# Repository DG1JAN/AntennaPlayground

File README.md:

# AntennaPlayground

In this Repro you will find several designs (mostly derived from my UniBaLun Project) to suport antenna building (EFHW and wire Dipols)

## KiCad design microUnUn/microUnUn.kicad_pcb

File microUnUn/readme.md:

# MicroUnUn
a PCB for a very lightweight qrp (maximum 10W SSB & CW or 5W on FT8) 1:49 UnUn

BOM:
- Amdion FT82-43 (FairRite 5943000601)
- 1m Enamel-coated copper wire (0.5mm to 0.7mm will be OK)
- 100pF Capaciator SMD 605 Type
- PCB-Edge Mount SMA Plug (also Socket for direct connection to the radio will work, but use a wire as counterpoise in this case!)
- 2mm "gold" Bana Plug 

You can also test a combination of FairRite 59430000601 and 5943001101 Torroids (see Pictzre below), According my measuremenst this results in a ~10% improved efficency over a FT82-43 or FT114-43). If you like pls have a look to my report:
https://github.com/DG1JAN/UniBalun/blob/main/20230620_EFHW_UnUn_efficiency_meas.pdf

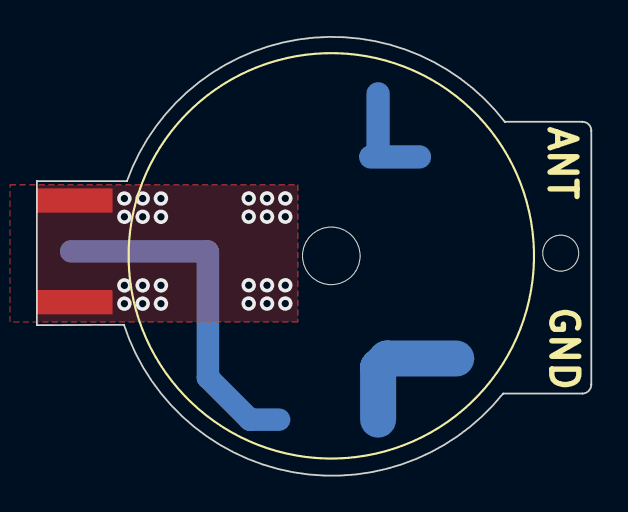
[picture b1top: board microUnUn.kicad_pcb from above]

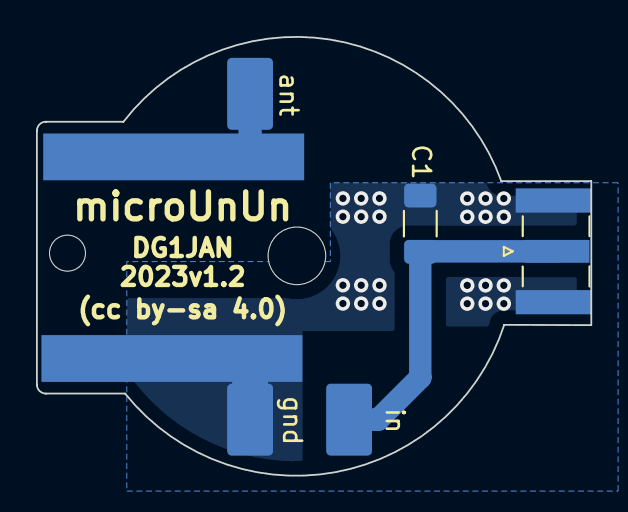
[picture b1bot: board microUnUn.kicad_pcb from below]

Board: 2 copper layers, 30.8 x 24.4 mm, 5 parts (4 on the bottom side), 3 nets.

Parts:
C1: 100pF; C_1206_3216Metric_Pad1.33x1.80mm_HandSolder
H1, H2: MountingHole_Pad; 2mmJack
J1: BNC; SMA_Samtec_SMA-J-P-X-ST-EM1_EdgeMount
U1: Core; FT82_Balun

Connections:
GND: C1.2, H2.1, J1.2 (Ext), U1.1 (gnd)
unnamed: C1.1, J1.1 (In), U1.2 (a)
unnamed: H1.1, U1.3 (x)

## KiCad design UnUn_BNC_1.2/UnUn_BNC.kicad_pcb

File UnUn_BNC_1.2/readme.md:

# UnUn_BNC
a PCB for a lightweight qrp (maximum 10W SSB & CW or 5W on FT8) 1:49  (or 1:9) UnUn
derived from my UniBalun Project (https://github.com/DG1JAN/UniBalun)

This PCB has the smal avantage over the UbiBalun, that you dont need need a jumper and that the "A" Pad on top is fixed connected to GND. So you
can add there a counterpois (esp. if used as 1:9 UnUn). 

BOM:
- Amdion FT82-43 (FairRite 5943000601) or FT114-43 (FairRite 5943001001)
- 1m Enamel-coated copper wire (0.5mm to 0.7mm will be fine, on the Ft114 also 1mm will fit)
- 100pF Capaciator, e.g. TDK CC45SL3FD101JYVNA
- BNC Socket, the Footprint supports multiple options:
    - Molex 73101
    - Amphenol B6252H7 / Telegärtner J01001A0038 (or similar)
    - PCB-Edge Mount SMA (e.g.
- 4mm "gold" Bana Plug (e.g. https://www.amazon.de/gp/product/B07VYSN74H/ref=ppx_yo_dt_b_asin_title_o01_s00?ie=UTF8&th=1)

You can also test a combination of FairRite 59430000601 and 5943001101 Torroids (see Pictzre below), According my measuremenst this results in a ~10% improved efficency over a FT82-43 or FT114-43). If you like pls have a look to my report:
https://github.com/DG1JAN/UniBalun/blob/main/20230620_EFHW_UnUn_efficiency_meas.pdf

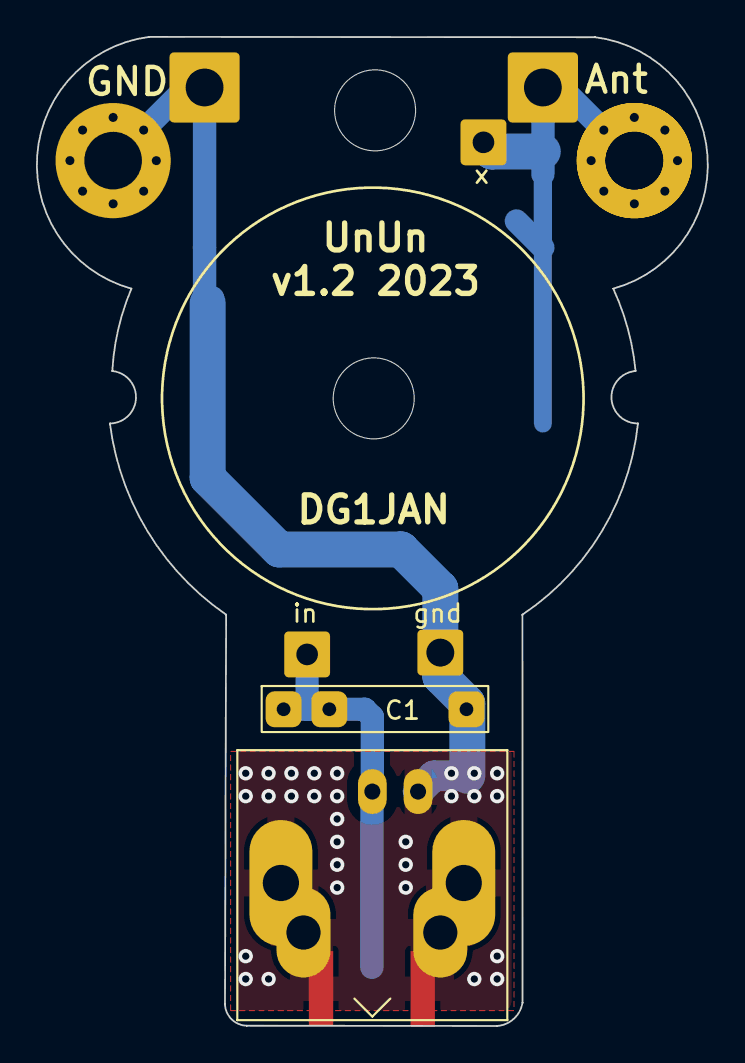
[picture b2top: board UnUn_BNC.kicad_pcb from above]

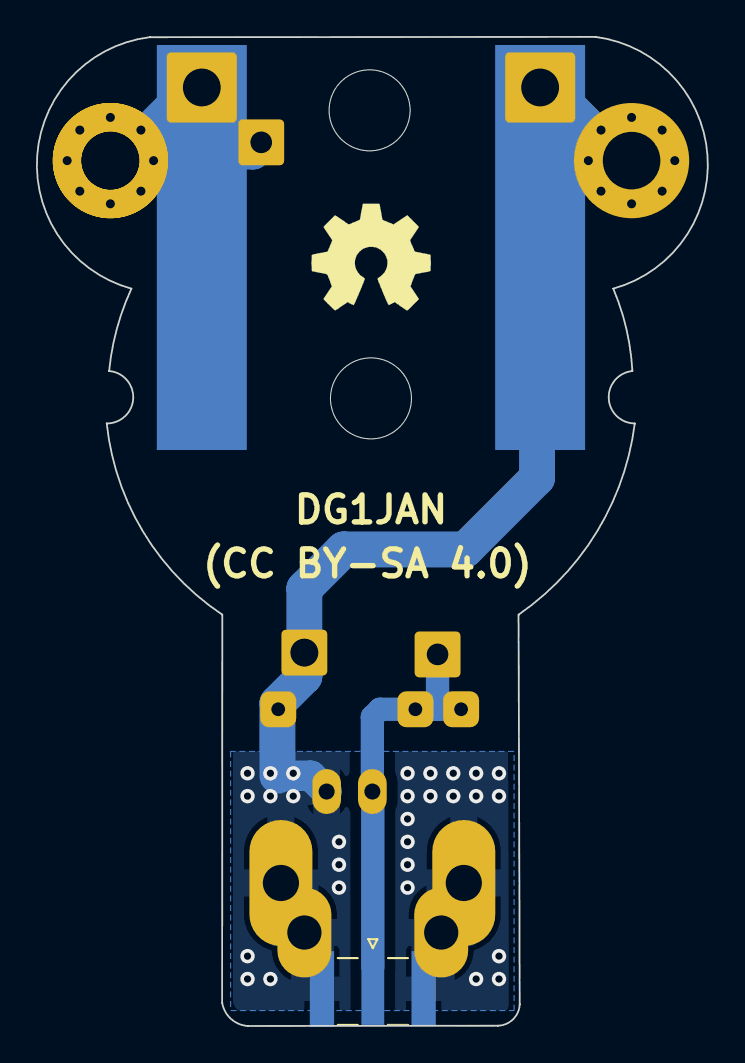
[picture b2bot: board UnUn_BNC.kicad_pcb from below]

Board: 2 copper layers, 37.3 x 55.0 mm, 10 parts (2 on the bottom side), 3 nets.

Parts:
C1: 100pF; THT_cap
H1: B; MountingHole_3.2mm_M3_Pad
H5, H5#2: MountingHole; MountingHole_4.5mm
J1: BNC; BNC_Amphenol_B6252HB-NPP3G-50_Horizontal
J3: B_THT_Pad; SolderWire-1.5sqmm_1x01_D1.7mm_OD3.9mm
J4: B_SMD_PAD; 4mmJack
J5: A_THT_Pad; SolderWire-1.5sqmm_1x01_D1.7mm_OD3.9mm
J6: A_SMD_PAD; 4mmJack
U2: Core; FT82_Balun

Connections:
GND: C1.2, J1.2 (Ext), J5.1, J6.1, U2.1 (a)
unnamed: C1.1, J1.1 (In), U2.4 (b')
unnamed: H1.1, J3.1, J4.1, U2.5 (x)

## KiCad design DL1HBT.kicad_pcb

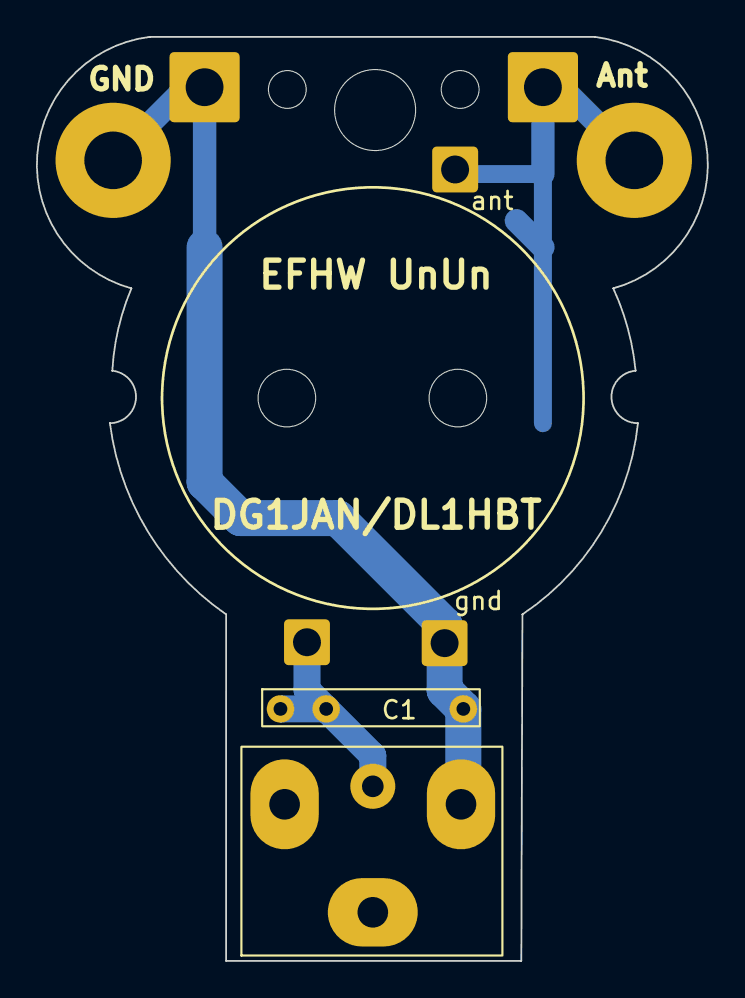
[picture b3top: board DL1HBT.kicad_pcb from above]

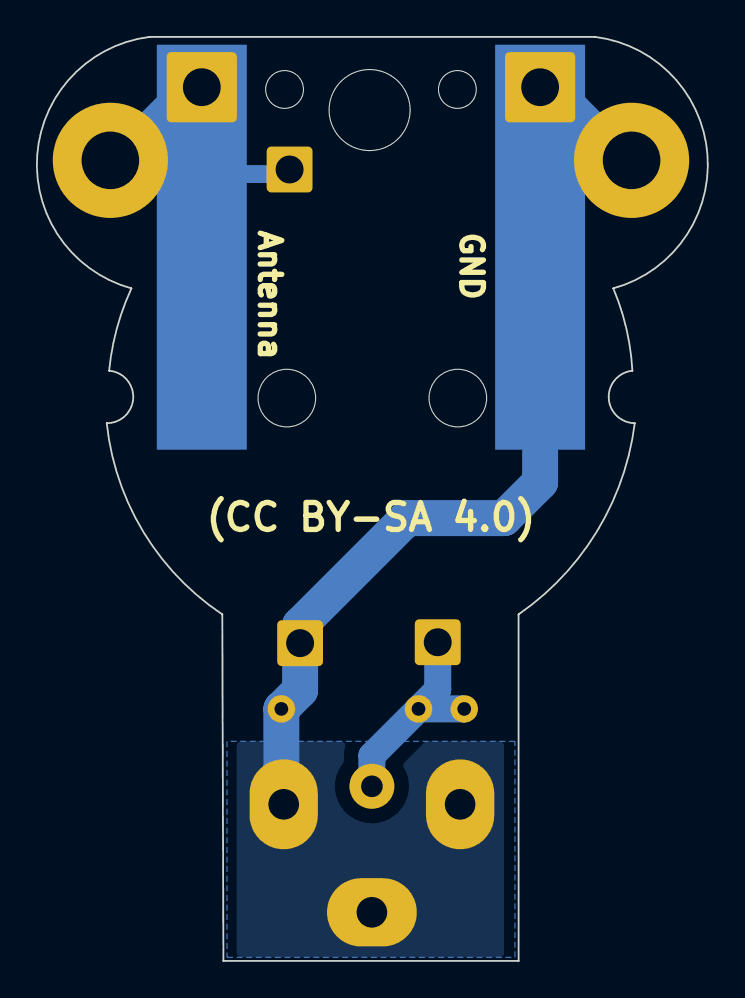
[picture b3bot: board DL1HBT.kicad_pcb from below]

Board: 2 copper layers, 37.3 x 51.3 mm, 12 parts (2 on the bottom side), 3 nets.

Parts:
C1: 100pF; THT_cap
H1: B; MountingHole_3.2mm_M3_Pad
H2: A; MountingHole_3.2mm_M3_Pad
H3, H4: MountingHole; MountingHole_2.1mm
H5: MountingHole; MountingHole_4.5mm
J1: BNC; Elecbee_BNC
J3: B_THT_Pad; SolderWire-1.5sqmm_1x01_D1.7mm_OD3.9mm
J4: B_SMD_PAD; 4mmJack
J5: A_THT_Pad; SolderWire-1.5sqmm_1x01_D1.7mm_OD3.9mm
J6: A_SMD_PAD; 4mmJack
U2: Core; FT82_Balun

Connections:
GND: C1.2, H2.1, J1.2 (Ext), J5.1, J6.1, U2.1 (gnd)
unnamed: C1.1, J1.1 (In), U2.2 (trx)
unnamed: H1.1, J3.1, J4.1, U2.3 (ant)

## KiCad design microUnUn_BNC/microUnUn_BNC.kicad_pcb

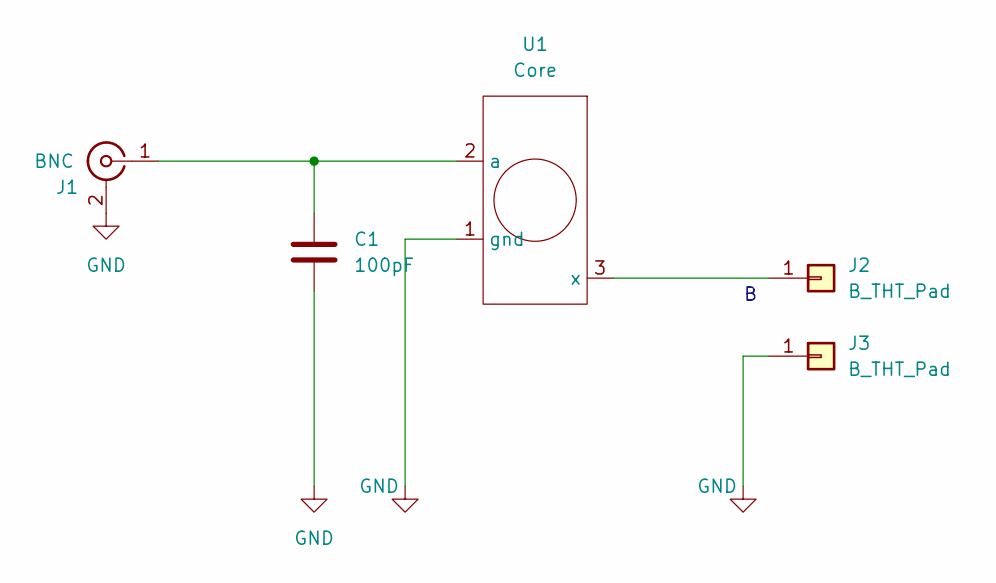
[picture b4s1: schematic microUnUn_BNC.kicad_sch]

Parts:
C1: 100pF; THTSMD_cap
J1: BNC; Elecbee_BNC
J2, J3: B_THT_Pad; SolderWire-1.5sqmm_1x01_D1.7mm_OD3.9mm
U1: Core; FT82_Balun

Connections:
GND: C1.2, J1.2 (Ext), J3.1, U1.1 (gnd)
unnamed: C1.1, J1.1 (In), U1.2 (a)
unnamed: J2.1, U1.3 (x)

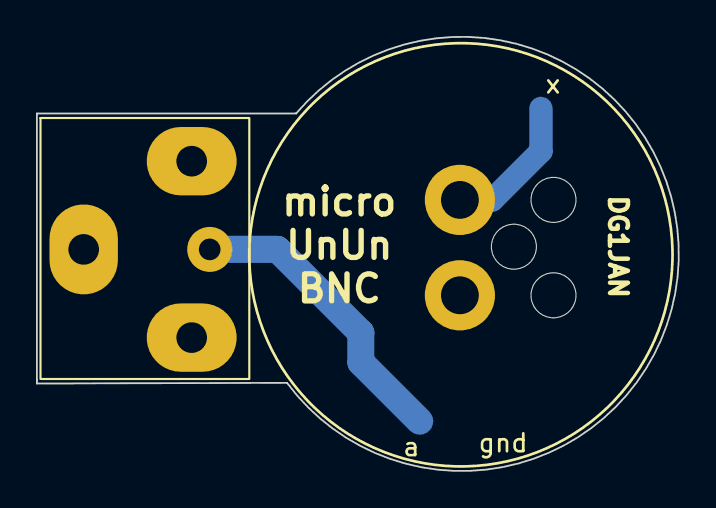
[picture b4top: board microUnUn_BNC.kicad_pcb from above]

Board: 2 copper layers, 35.7 x 24.1 mm, 5 parts (1 on the bottom side), 3 nets.

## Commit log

2022-09-28 rearanging structure in Repro
2022-09-28 update with BNC
2022-09-28 upload
2023-08-31 cleanup
2023-08-31 v1.2

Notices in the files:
DL1HBT.kicad_pcb:
(CC BY-SA 4.0)
